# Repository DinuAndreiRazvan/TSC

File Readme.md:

# eBook Project - Autodesk Fusion 360 

## Images

*Complete View*

*Exploded View*

*PCB*

## Block Diagram

## Bill of Materials

| Component | Description | Datasheet | Shop |
|-----------|-------------|-----------|------|
| ESP32-C6-WROOM-1-N8 | Wi-Fi, BLE, Zigbee SoC Module | [Datasheet](https://www.espressif.com/sites/default/files/documentation/esp32-c6-wroom-1_wroom-1u_datasheet_en.pdf) | [Shop](https://eu.mouser.com/ProductDetail/Espressif-Systems/ESP32-C6-WROOM-1U-N8?qs=1Kr7Jg1SGW%2FzPU4G%252ByMwkA%3D%3D) |
| MCP73831 | Li-Po Battery Charging Controller | [Datasheet](https://eu.mouser.com/datasheet/2/268/MCP73831_Family_Data_Sheet_DS20001984H-3441711.pdf) | [Shop](https://eu.mouser.com/ProductDetail/Microchip-Technology/MCP73831T-2ACI-OT?qs=yUQqVecv4qvbBQBGbHx0Mw%3D%3D) |
| XC6220A331MR-G | LDO Voltage Regulator | [Datasheet](https://eu.mouser.com/datasheet/2/760/xc6220-3371556.pdf) | [Shop](https://eu.mouser.com/ProductDetail/Torex-Semiconductor/XC6220A331MR-G?qs=AsjdqWjXhJ8ZSWznL1J0gg%3D%3D) |
| BME680 | Environmental Sensor | [Datasheet](https://eu.mouser.com/datasheet/2/783/BST_BME680_DS001-1509608.pdf) | [Shop](https://eu.mouser.com/ProductDetail/Bosch-Sensortec/BME680?qs=v271MhAjFHjo0yA%2FC4OnDQ%3D%3D) |
| DS3231SN | Real-Time Clock | [Datasheet](https://eu.mouser.com/datasheet/2/609/DS3231-3421123.pdf) | [Shop](https://eu.mouser.com/ProductDetail/Analog-Devices-Maxim-Integrated/DS3231SN?qs=1eQvB6Dk1vhUlr8%2FOrV0Fw%3D%3D) |
| MAX17048G+T10 | Battery Fuel Gauge | [Datasheet](https://eu.mouser.com/datasheet/2/609/MAX17048_MAX17049-3469099.pdf) | [Shop](https://eu.mouser.com/ProductDetail/Analog-Devices-Maxim-Integrated/MAX17048G%2bT10?qs=D7PJwyCwLAoGnnn8jEPRBQ%3D%3D) |
| W25Q512JVEIQ | 512Mb Flash Memory | [Datasheet](https://eu.mouser.com/datasheet/2/949/Winbond_W25Q512JV_Datasheet-3240039.pdf) | [Shop](https://eu.mouser.com/ProductDetail/Winbond/W25Q512JVEIQ?qs=l7cgNqFNU1jw6svr3at6tA%3D%3D) |
| USB4110-GF-A | USB Type-C Connector | [Datasheet](https://eu.mouser.com/datasheet/2/837/GCT_USB4110_Product_Drawing___20k_cycles-3455479.pdf) | [Shop](https://eu.mouser.com/ProductDetail/GCT/USB4110-GF-A?qs=KUoIvG%2F9IlYiZvIXQjyJeA%3D%3D) |
| 112A-TAAR-R03 | Micro SD Card Connector | [Datasheet](https://www.attend.com.tw/data/download/file/112A-TAAR-R03_Spec.pdf) | [Shop](https://www.tme.eu/ro/details/mcc-sdmicro/conectori-pentru-cartele/attend/112a-taar-r03/) |
| SI1308EDL-T1-GE3 | N-Channel MOSFET | [Datasheet](https://www.vishay.com/docs/63399/si1308edl.pdf) | [Shop](https://eu.mouser.com/ProductDetail/Vishay-Semiconductors/SI1308EDL-T1-GE3?qs=bX1%252BNvsK%2FBramh9tgpOaEw%3D%3D) |
| DMG2305UX-7 | P-Channel MOSFET | [Datasheet](https://www.diodes.com/assets/Datasheets/DMG2305UX.pdf) | [Shop](https://eu.mouser.com/ProductDetail/Diodes-Incorporated/DMG2305UX-7?qs=L1DZKBg7t5F%2FNBHrjfxC%252Bg%3D%3D) |
| USBLC6-2SC6Y | USB ESD Protection | [Datasheet](https://eu.mouser.com/datasheet/2/389/usblc6_2sc6y-1852505.pdf) | [Shop](https://eu.mouser.com/ProductDetail/STMicroelectronics/USBLC6-2SC6Y?qs=gNDSiZmRJS%2FOgDexvXkdow%3D%3D) |
| CPH3225 | 11mF Supercapacitor | [Datasheet](https://eu.mouser.com/datasheet/2/360/Seiko_Instruments_MicroBattery_E_20230330_2024Jan_-3561061.pdf) | [Shop](https://eu.mouser.com/ProductDetail/Seiko-Semiconductors/CPH3225A?qs=3etwrb1wR%252BhUOph6lAO7eg%3D%3D) |
| Waveshare Display | 7.5" E-Ink | [Datasheet](https://files.waveshare.com/upload/6/60/7.5inch_e-Paper_V2_Specification.pdf) | [Shop](https://www.waveshare.com/7.5inch-e-paper-hat.htm) |
| Cellevia Battery | Polymer Lithium-Ion | [Datasheet](https://www.tme.eu/Document/e0683d8c34e6d878124489f71bffb6ee/cel0014.pdf) | [Shop](https://www.emag.ro/acumulator-litiu-polymer-cellevia-3-7v-1800mah-accu-lp364778-c/pd/DVCNMRBBM/) | 
| MBR0530 | Schottky Diode | [Datasheet](https://www.onsemi.com/download/data-sheet/pdf/mbr0530t1-d.pdf) | [Shop](https://eu.mouser.com/ProductDetail/onsemi/MBR0530T3G?qs=3JMERSakebpEmdUS6GetdQ%3D%3D) |
| CC0402 | Capacitor | [Datasheet](https://eu.mouser.com/datasheet/2/447/upy_gphc_x5r_4v_to_50v-3461255.pdf) | [Shop](https://eu.mouser.com/ProductDetail/YAGEO/CC0402KRX5R6BB105?qs=BKNoF%2F0xMNu0TvpE6ze2Iw%3D%3D) | 
| RR0402 | Resistor | [Datasheet](https://www.vishay.com/docs/28952/mcs0402at-mct0603at-mcu0805at-mca1206at.pdf) | [Shop](https://eu.mouser.com/ProductDetail/Vishay-Beyschlag/MCS0402MD1002BE100?qs=sGAEpiMZZMvdGkrng054twsDrRiZGhrjpqs%252BW5FxlP8%3D) |

## Hardware Functionality

### Power Management
The device can be powered in multiple ways:
- **USB Power**: Through USB-C connector (USB4110-GF-A) with ESD protection (USBLC6-2SC6Y)
- **LiPo Battery**: Charged via MCP73831 controller with status LED
- **Supercapacitor Backup**: CPH3225A for maintaining functionality during power transitions

The power path includes:
- XC6220A331MR-G LDO provides stable 3.3V to the system
- MAX17048G+T10 monitors battery capacity
- P-channel MOSFETs (DMG2305UX-7) for power path selection
- Schottky diodes (MBR0530) for reverse voltage protection

### Processing & Memory
- **ESP32-C6-WROOM-1-N8**: Main microcontroller with Wi-Fi 6, Bluetooth 5, and Zigbee 3.0 capabilities
- **W25Q512JVEIQ**: 512Mb external SPI flash memory for data storage
- **SD Card Slot**: For user data storage and expansion

### Display System
- 7.5 inch E-Paper display interfaced via SPI
- Multiple capacitors for drive stability and voltage management

### Sensors
- **BME680/BME688**: I²C environmental sensor measuring:
    - Temperature: -40 to +85°C
    - Humidity: 0-100% RH
    - Pressure: 300-1100 hPa
    - Air Quality (gas resistance)
- **DS3231SN**: Highly accurate I²C real-time clock with temperature compensation

### Connectivity
- **USB-C**: For programming, data transfer, and charging
- **Qwiic/STEMMA QT**: I²C connector for external sensors/accessories
- **SD Card**: For data storage expansion

### User Interface
- **Reset Button**: For restarting the system
- **Boot Button**: For entering bootloader mode
- **Change Button**: For user interaction with the displayed content

## ESP32-C6 Pinout Configuration

| ESP32-C6 Pin | Function | Connected Component | Interface |
|--------------|----------|---------------------|-----------|
| EN | Reset | RESET_BUTTON | Digital Input |
| GPIO 0 | INT_RTC | DS3231SN | Interrupt |
| GPIO 1 | 32 khz | DS3231SN | Clock Output |
| GPIO 2 | MISO | SPI Bus | SPI |
| GPIO 3 | E-Paper BUSY | E-Paper Display | Digital Input |
| GPIO 4 | SD Card CS | SD Card Slot | SPI |
| GPIO 5 | E-Paper DC | E-Paper Display | Digital Output |
| GPIO 6 | SCK - Clock | SPI Bus | SPI |
| GPIO 7 | MOSI | SPI Bus | SPI |
| GPIO 9 | IO/Boot | BOOT_BUTTON | Digital Input |
| GPIO 10 | E-Paper CS | E-Paper Display | SPI |
| GPIO 11 | Flash CS | W25Q512JVEIQ | SPI |
| GPIO 12 | USB_D- | USB Interface | USB |
| GPIO 13 | USB_D+ | USB Interface | USB |
| GPIO 15 | IO/Change | CHANGE_BUTTON | Digital Input |
| GPIO 16 | TX | USB-to-Serial | UART |
| GPIO 17 | RX | USB-to-Serial | UART |
| GPIO 18 | RTC Reset | DS3231SN | Digital Output |
| GPIO 19 | I2C_PW | I²C Power Control | Digital Output |
| GPIO 20 | EPD_3V3_C | E-Paper Display Power | Power Control |
| GPIO 21 | SDA | I²C Bus (BME680, RTC) | I²C |
| GPIO 22 | SCL | I²C Bus (BME680, RTC) | I²C |
| GPIO 23 | E-Paper RESET | E-Paper Display | Digital Output |

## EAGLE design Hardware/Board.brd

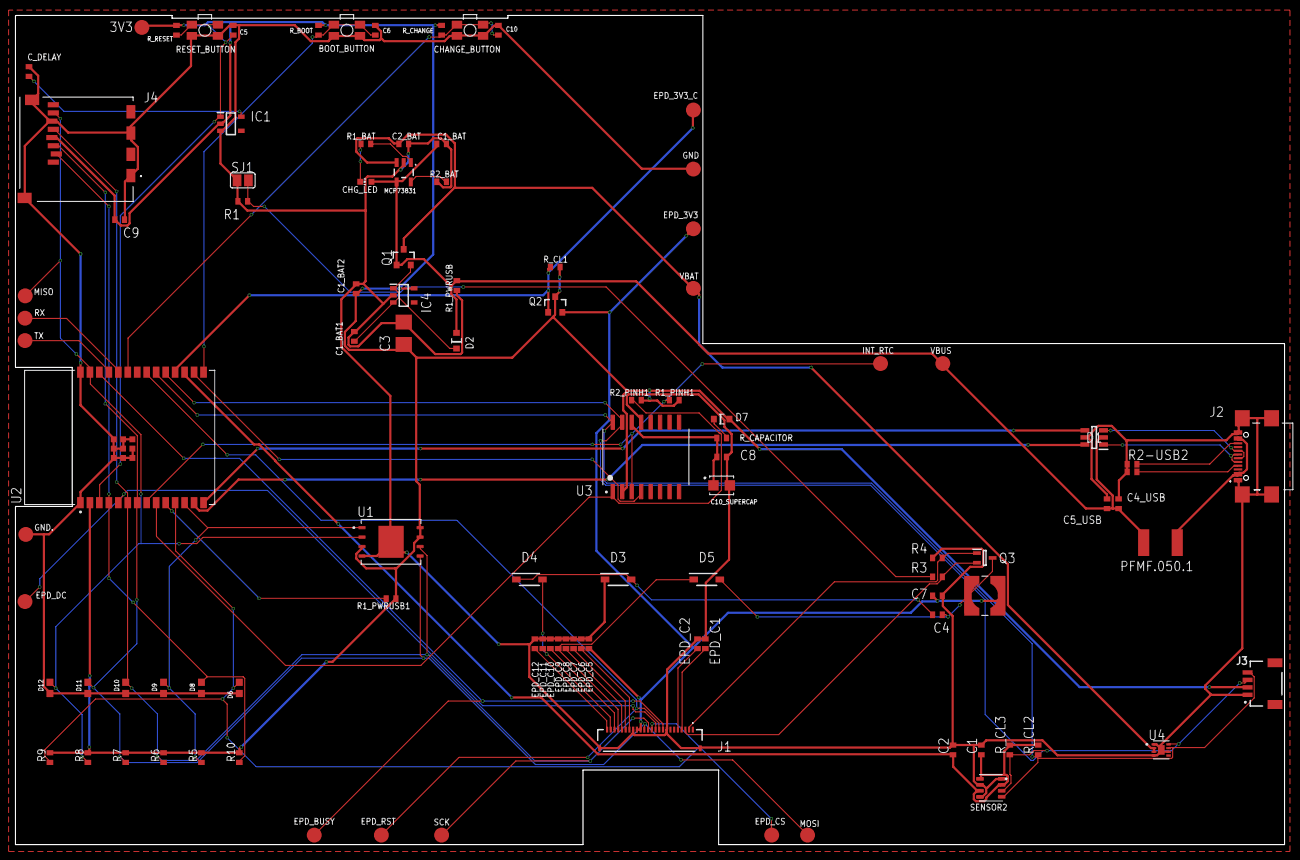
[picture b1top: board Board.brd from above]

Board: 2 copper layers, 170.2 x 111.2 mm, 103 parts (0 on the bottom side), 55 nets.

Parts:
3V3: TPTP20R; TP20R
BOOT_BUTTON: BUTTON_CUSYOMV1; MYBUTTON
C1, C2, C6, C8, C10: 100nF; EAGLE-LTSPICE_C0402
C1_BAT, C1_BAT1, C1_BAT2, C2_BAT: 4.7uF; EAGLE-LTSPICE_C0402
C3: 100uF TANT; RCL_CT3528
C4: 4.7uF/25V; EAGLE-LTSPICE_C0402
C4_USB, C9: 100nF; ESP32_WROVER_EAGLE-LTSPICE_C0402
C5: 1uF; EAGLE-LTSPICE_C0402
C5_USB: 4.7uF; ESP32_WROVER_EAGLE-LTSPICE_C0402
C7: 10uF; EAGLE-LTSPICE_C0402
C10_SUPERCAP: CPH3225A; CAPCP3225X100N
CHANGE_BUTTON: BUTTON_CUSYOMV1; MYBUTTON
CHG_LED: ADAFRUIT_CHIP-LED0603
C_DELAY: 100nF; EAGLE-LTSPICE_C0402
D1: USBLC6-2SC6Y; SOT95P280X145-6N
D2, D7: ESP32_WROVER_AVX---SD0805S020S1R0_AVX_SD0805S020S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; ESP32_WROVER_AVX---SD0805S020S1R0_AVX_SD0805S020S1R0_0
D3, D4, D5: MBR0530; SOD3716X135N
D6, D8, D9, D10, D11, D12: PGB1010603MR; DIOC1608X36N
EPD_3V3, EPD_3V3_C: TPTP20R; TP20R
EPD_BUSY: TPTP20R; TP20R
EPD_C1, EPD_C2, EPD_C5, EPD_C6, EPD_C7, EPD_C8, EPD_C9, EPD_C10, EPD_C11, EPD_C12: 1uF/50V; EAGLE-LTSPICE_C0402
EPD_CS: TPTP20R; TP20R
EPD_DC: TPTP20R; TP20R
EPD_RST: TPTP20R; TP20R
GND, GND.: TPTP20R; TP20R
IC1: BD5229G-TR; SOT95P280X125-5N
IC4: XC6220A331MR-G; SOT95P280X120-5N
INT_RTC: TPTP20R; TP20R
J1: FH34SRJ-24S-0.5SH_99_; FH34SRJ24S05SH99
J2: SAMACSYS_PARTS_USB4110-GF-A; SAMACSYS_PARTS_USB4110GFA
J3: QWIIC_RIGHT_ANGLE; JST04_1MM_RA
J4: 112A-TAAR-R03_ATTEND; 112ATAARR03ATTEND
L1: 744043680IND_4828-WE-TPC_WRE; IND_4828-WE-TPC_WRE
MCP73831: ESP32_WROVER_SPARKFUN-IC-POWER_MCP73831; ESP32_WROVER_SPARKFUN-IC-POWER_SOT23-5
MISO: TPTP20R; TP20R
MOSI: TPTP20R; TP20R
PFMF.050.1: ESP32C6_VARISTORCN1812; ESP32C6_VARISTOR_CT/CN1812
Q1, Q2: 20V/4.2A/52mΩ/1.4W; ESP32_WROVER_SPARKFUN-DISCRETESEMI_SOT23-3
Q3: SI1308EDL-T1-GE3; SOT65P210X110-3N
R1: 2.2; ESP32_WROVER_EAGLE-LTSPICE_R0402
R1_BAT: 200; ESP32_WROVER_EAGLE-LTSPICE_R0402
R1_PINH1, R2_PINH1, R4, R5, R6, R7, R8, R9, R10: 10k; ESP32_WROVER_EAGLE-LTSPICE_R0402
R1_PWRUSB, R1_PWRUSB1: 100k; ESP32_WROVER_EAGLE-LTSPICE_R0402
R2-USB1, R2-USB2: 5k1; ESP32_WROVER_EAGLE-LTSPICE_R0402
R2_BAT: 2k; ESP32_WROVER_EAGLE-LTSPICE_R0402
R3: 0.47; ESP32_WROVER_EAGLE-LTSPICE_R0402
RESET_BUTTON: BUTTON_CUSYOMV1; MYBUTTON
RX: TPTP20R; TP20R
R_BOOT: 10k; ESP32_WROVER_EAGLE-LTSPICE_R0402
R_CAPACITOR: 15; ESP32_WROVER_EAGLE-LTSPICE_R0402
R_CHANGE: 10k; ESP32_WROVER_EAGLE-LTSPICE_R0402
R_CL1, R_CL2, R_CL3: 10k; ESP32_WROVER_EAGLE-LTSPICE_R0402
R_RESET: 10k; ESP32_WROVER_EAGLE-LTSPICE_R0402
SCK: TPTP20R; TP20R
SENSOR2: ESP32_WROVER_BME680_BME680; ESP32_WROVER_BME680_PSON80P300X300X100-8N
SJ1: SJ
TX: TPTP20R; TP20R
U1: W25Q512JVEIQ; SON127P600X800X80-9N
U2: ESP32-C6-WROOM-1-N8; XCVR_ESP32-C6-WROOM-1-N8
U3: DS3231SN#; SOIC127P1032X265-16N
U4: MAX17048G+T10; SON50P200X200X80-9N
VBAT: TPTP20R; TP20R
VBUS: TPTP20R; TP20R

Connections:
3V3: 3V3.TP, C1_BAT2.1, C3.+, C9.1, D7.2, IC1.2, IC4.5, J3.2, J4.P4, Q2.3, R1_PINH1.2, R1_PWRUSB1.2, R2_PINH1.2, R5.2, R6.2, R7.2, R8.2, R9.2, R10.2, R_BOOT.2, R_CHANGE.2, R_CL1.2, R_RESET.2, U1.3, U1.7, U1.8, U2.2, U3.2
32KHZ: R2_PINH1.1, U2.9, U3.1
DN: D1.1, J2.A7, J2.B7
DP: D1.3, J2.A6, J2.B6
EPD_3V3: C7.1, EPD_3V3.TP, EPD_C5.2, J1.15, J1.16, L1.2, Q2.2
EPD_3V3_C: EPD_3V3_C.TP, Q2.1, R_CL1.1, U2.18
EPD_BUSY: EPD_BUSY.TP, J1.9, U2.26
EPD_CS: D6.2, EPD_CS.TP, J1.12, R9.1, U2.11
EPD_DC: EPD_DC.TP, J1.11, U2.5
EPD_RST: EPD_RST.TP, J1.10, U2.21
FLASH_CS: D9.2, R5.1, U1.1, U2.12
GDR: J1.2, Q3.1, R4.2
GND: BOOT_BUTTON.1, BOOT_BUTTON.2, C1.2, C1_BAT.2, C1_BAT1.2, C1_BAT2.2, C2.2, C2_BAT.2, C3.-, C4_USB.2, C5.2, C5_USB.2, C6.2, C7.2, C8.2, C9.2, C10.2, C10_SUPERCAP.2, CHANGE_BUTTON.1, CHANGE_BUTTON.2, C_DELAY.2, D1.5, D3.1, D6.1, D8.1, D9.1, D10.1, D11.1, D12.1, EPD_C1.1, EPD_C2.1, EPD_C5.1, EPD_C6.1, EPD_C7.1, EPD_C8.1, EPD_C9.1, EPD_C10.1, EPD_C11.1, EPD_C12.1, GND.TP, GND..TP, IC1.3, IC4.2, J1.8, J1.17, J1.MP1, J1.MP2, J2.A1, J2.A12, J2.B1, J2.B12, J2.MP1, J2.MP2, J2.MP3, J2.MP4, J3.1, J4.G1, J4.G2, J4.G3, J4.G4, J4.P6, MCP73831.2, R1.1, R1_PWRUSB.1, R2-USB1.1, R2-USB2.1, R2_BAT.1, R4.1, RESET_BUTTON.1, RESET_BUTTON.2, SENSOR2.1, SENSOR2.5, SENSOR2.7, SJ1.1, U1.4, U1.9, U2.1, U2.28, U2.29_1, U2.29_2, U2.29_3, U2.29_4, U2.29_5, U2.29_6, U2.29_7, U2.29_8, U2.29_9, U3.13, U4.1, U4.4, U4.6, U4.9
GPIO8: R1_PWRUSB1.1, U2.10
I2C_PW: C1.1, C2.1, R_CL2.2, R_CL3.2, SENSOR2.2, SENSOR2.6, SENSOR2.8, U2.17
INT_RTC: INT_RTC.TP, R1_PINH1.1, U2.8, U3.3
IO/BOOT: BOOT_BUTTON.3, BOOT_BUTTON.4, C6.1, R_BOOT.1, U2.15
IO/CHANGE: C10.1, CHANGE_BUTTON.3, CHANGE_BUTTON.4, R_CHANGE.1, U2.23
MISO: D12.2, J4.P7, MISO.TP, R8.1, U1.2, U2.27
MOSI: D11.2, J1.14, J4.P3, MOSI.TP, R7.1, U1.5, U2.7
unnamed: J2.A5, R2-USB1.2
unnamed: J2.B5, R2-USB2.2
unnamed: C1_BAT1.1, D2.1, IC4.1, IC4.3, Q1.2
unnamed: CHG_LED.C, R1_BAT.1
unnamed: MCP73831.5, R2_BAT.2
unnamed: C4.1, D3.2, D4.1
unnamed: MCP73831.1, R1_BAT.2
unnamed: EPD_C12.2, J1.24
unnamed: C_DELAY.1, IC1.5
unnamed: EPD_C10.2, J1.22
unnamed: EPD_C1.2, J1.4
unnamed: EPD_C2.2, J1.5
unnamed: D7.1, R_CAPACITOR.2
unnamed: EPD_C8.2, J1.20
unnamed: EPD_C7.2, J1.19
unnamed: EPD_C6.2, J1.18
PREVGH: D5.1, EPD_C9.2, J1.21
PREVGL: D4.2, EPD_C11.2, J1.23
RESE: J1.3, Q3.2, R3.2
RESE': R1.2, R3.1, SJ1.2
RESET: C5.1, IC1.1, RESET_BUTTON.3, RESET_BUTTON.4, R_RESET.1, U2.3
RTC_RST: U2.16, U3.4
RX: RX.TP, U2.24
SCK: D10.2, J1.13, J4.P5, R6.1, SCK.TP, U1.6, U2.6
SCL: J3.4, R_CL2.1, SENSOR2.4, U2.20, U3.16, U4.7
SDA: J3.3, R_CL3.1, SENSOR2.3, U2.19, U3.15, U4.8
SRC: C4.2, D5.2, L1.1, Q3.3
SS_SD: D8.2, J4.P2, R10.1, U2.4
TX: TX.TP, U2.25
USB_D+: D1.4, U2.14
USB_D-: D1.6, U2.13
VBAT: C2_BAT.1, MCP73831.3, Q1.3, U4.2, U4.3, VBAT.TP
VBUS: C1_BAT.1, C4_USB.1, C5_USB.1, CHG_LED.A, D1.2, D2.2, MCP73831.4, PFMF.050.1.2, Q1.1, R1_PWRUSB.2, VBUS.TP
VRTC: C8.1, C10_SUPERCAP.1, R_CAPACITOR.1, U3.14
VUSB: J2.A4, J2.A9, J2.B4, J2.B9, PFMF.050.1.1

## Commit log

2025-03-17 init
2025-03-22 completed half of the Schematics
2025-04-06 removed old files
2025-04-06 Readme updates
2025-04-06 Block Diagram added
2025-04-06 Block Diagram updated
2025-04-11 Solved 3D models issues, named the Test Pads accordingly and and removed component values from the PCB

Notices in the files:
parts and their libraries:
COPYRIGHT: Copyright (C) 2024 Ultra Librarian. All rights reserved.
